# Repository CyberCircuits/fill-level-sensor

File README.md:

Fill-level-sensor
=================

Projects files for roving dynamics ltd, open source fill level sensor (Eagle CAD and MPLAB XC32)

Full details of project can be found at www.rodyne.com

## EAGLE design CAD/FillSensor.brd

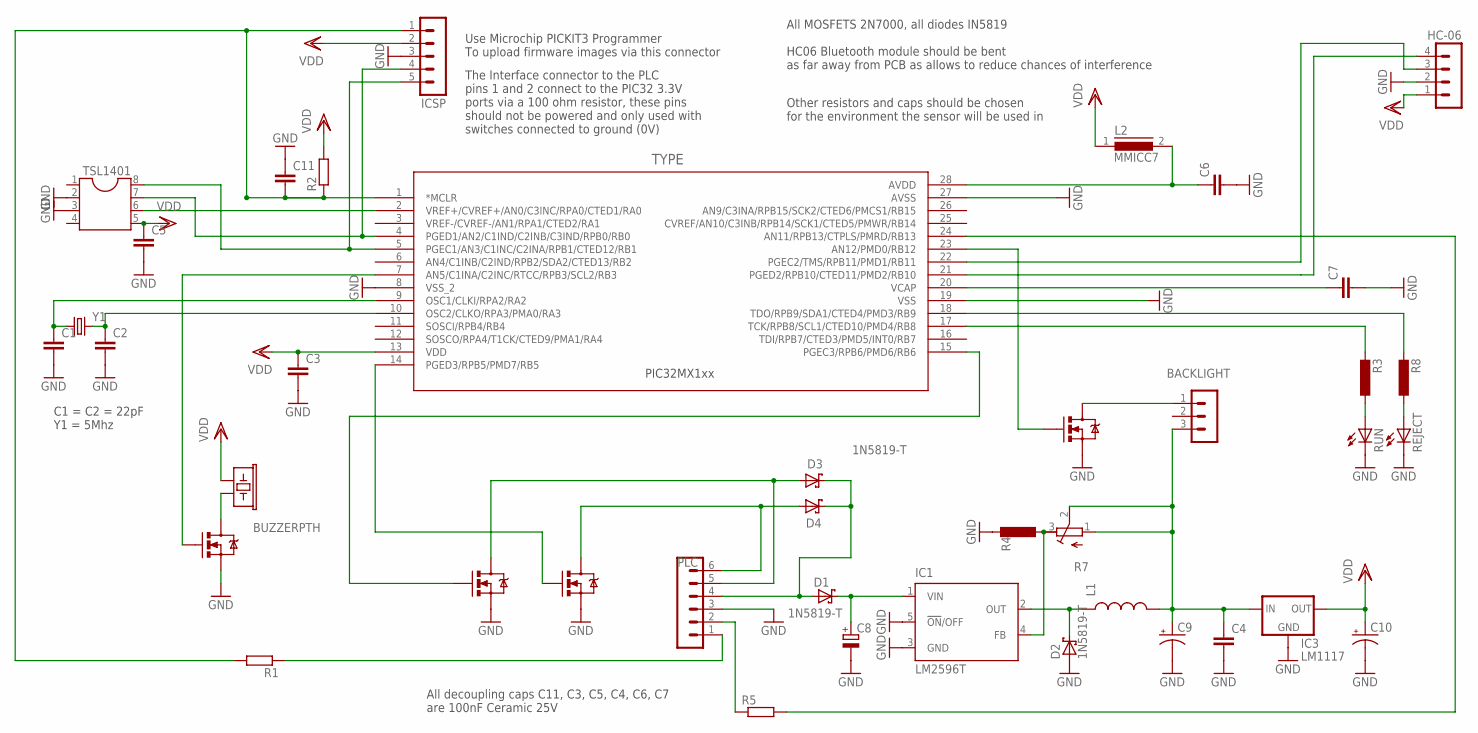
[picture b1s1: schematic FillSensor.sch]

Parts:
BACKLIGHT: MA03-1
C1, C2, C3, C4, C5, C6, C7, C11: CAPPTH; CAP-PTH-SMALL
C8: CPOL-EUE5-5; E5-5
C9, C10: CAP_POLPTH2; CPOL-RADIAL-10UF-25V
D1, D2, D3, D4: 1N5819-T; DO41-7.6
HC-06: MA04-1
IC1: LM2596T; T05D; MPN LM2596T-ADJ/LF02
IC3: LM1117; TO252
ICSP: MA05-1
L1: INDUCTORPWR; CDRH125
L2: MMICC7
PLC: MA06-1
Q1, Q2, Q3, Q4: MOSFET-NCHANNEL2N7000; TO-92-AMMO
R1, R2, R5: R-EU_0207/10; 0207/10
R3, R4, R8: L-EU0207/10; 0207/10
R7: R-TRIMM64W; RTRIM64W
REJECT: LED5MM
RUN: LED5MM
SG1: BUZZERPTH; BUZZER-12MM
TSL1401: DIL8; DIL08
U1: PIC32MX150F128B-; SPDIP28_300MC
Y1: CRYSTALHC49UV; HC49U-V

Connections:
GND: C1.2, C2.2, C3.2, C4.2, C5.2, C6.2, C7.2, C8.-, C9.2 (-), C10.2 (-), C11.1, D2.A, HC-06.2, IC1.3 (GND), IC1.5 (!ON!/OFF), IC3.1 (GND), ICSP.3, PLC.3, Q1.1 (S), Q2.1 (S), Q3.1 (S), Q4.1 (S), R4.1, REJECT.K (C), RUN.K (C), TSL1401.2, TSL1401.3, U1.8 (VSS_2), U1.19 (VSS), U1.27 (AVSS)
unnamed: C1.1, U1.9 (OSC1/CLKI/RPA2/RA2), Y1.1
unnamed: C2.1, U1.10 (OSC2/CLKO/RPA3/PMA0/RA3), Y1.2
unnamed: C6.1, L2.2, U1.28 (AVDD)
unnamed: C11.2, ICSP.1, R1.2, R2.1, U1.1 (*MCLR)
unnamed: TSL1401.6, U1.2 (VREF+/CVREF+/AN0/C3INC/RPA0/CTED1/RA0)
unnamed: R3.1, RUN.A
unnamed: ICSP.5, TSL1401.8, U1.5 (PGEC1/AN3/C1INC/C2INA/RPB1/CTED12/RB1)
unnamed: C7.1, U1.20 (VCAP)
unnamed: Q3.2 (G), U1.23 (AN12/PMD0/RB12)
unnamed: R5.2, U1.24 (AN11/RPB13/CTPLS/PMRD/RB13)
unnamed: ICSP.4, TSL1401.7, U1.4 (PGED1/AN2/C1IND/C2INB/C3IND/RPB0/RB0)
unnamed: R8.1, REJECT.A
unnamed: C8.+, D1.C, IC1.1 (VIN)
unnamed: HC-06.3, U1.22 (PGEC2/TMS/RPB11/PMD1/RB11)
unnamed: IC1.4 (FB), R4.2, R7.3 (A)
unnamed: D4.A, PLC.6, Q1.3 (D)
unnamed: D3.A, PLC.5, Q2.3 (D)
unnamed: Q2.2 (G), U1.15 (PGEC3/RPB6/PMD6/RB6)
unnamed: Q1.2 (G), U1.14 (PGED3/RPB5/PMD7/RB5)
unnamed: BACKLIGHT.3, C4.1, C9.1 (+), IC3.2 (IN), L1.2, R7.1 (E), R7.2 (S)
unnamed: R3.2, U1.17 (TCK/RPB8/SCL1/CTED10/PMD4/RB8)
unnamed: R8.2, U1.18 (TDO/RPB9/SDA1/CTED4/PMD3/RB9)
unnamed: BACKLIGHT.1, Q3.3 (D)
unnamed: HC-06.4, U1.21 (PGED2/RPB10/CTED11/PMD2/RB10)
unnamed: Q4.3 (D), SG1.- (2)
unnamed: Q4.2 (G), U1.7 (AN5/C1INA/C2INC/RTCC/RPB3/SCL2/RB3)
unnamed: D1.A, D3.C, D4.C, PLC.4
unnamed: PLC.1, R1.1
unnamed: PLC.2, R5.1
TH1: D2.C, IC1.2 (OUT), L1.1
VDD: C3.1, C5.1, C10.1 (+), HC-06.1, IC3.TAB (OUT), ICSP.2, L2.1, R2.2, SG1.+ (1), TSL1401.5, U1.13 (VDD)

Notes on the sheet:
PIC32MX1xx
Use Microchip PICKIT3 Programmer To upload firmware images via this connector
All MOSFETS 2N7000, all diodes IN5819 HC06 Bluetooth module should be bent as far away from PCB as allows to reduce chances of interference
C1 = C2 = 22pF Y1 = 5Mhz
All decoupling caps C11, C3, C5, C4, C6, C7 are 100nF Ceramic 25V
The Interface connector to the PLC pins 1 and 2 connect to the PIC32 3.3V ports via a 100 ohm resistor, these pins should not be powered and only used with switches connected to ground (0V)
Other resistors and caps should be chosen for the environment the sensor will be used in

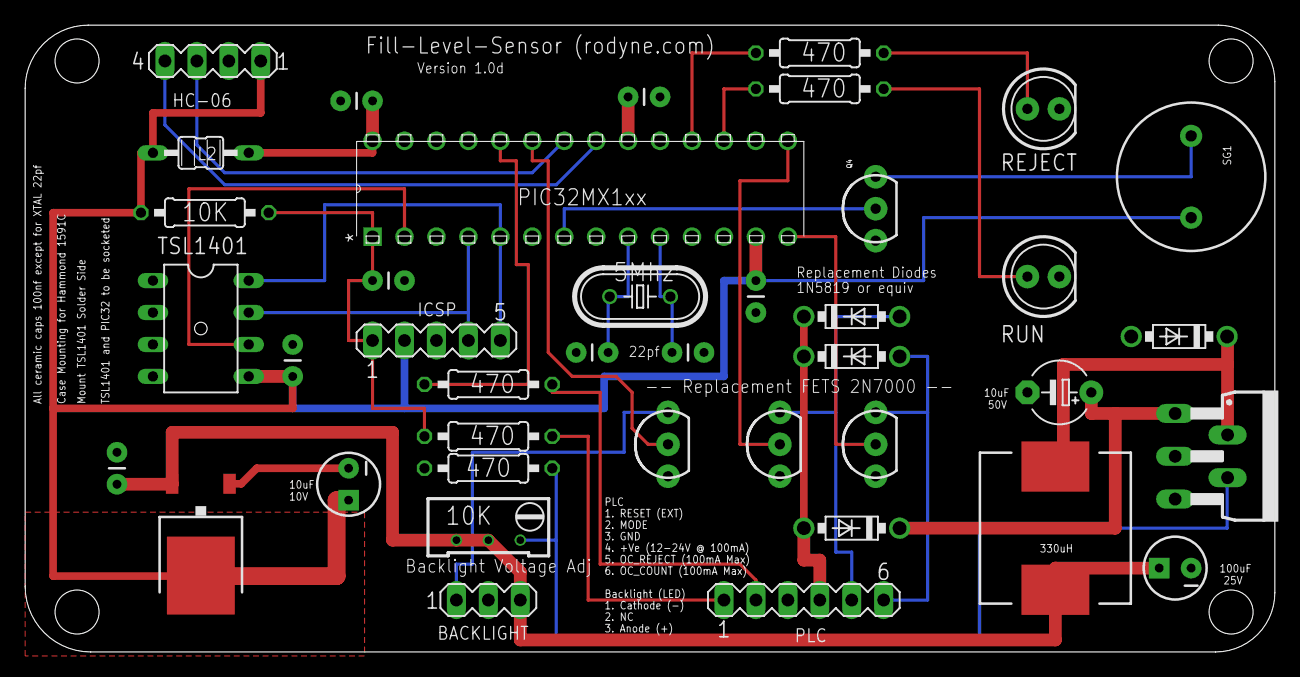
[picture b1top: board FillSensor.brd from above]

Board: 4 copper layers, 99.4 x 49.8 mm, 40 parts (0 on the bottom side), 32 nets.

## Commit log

2014-01-07 Added Working File set from Local PC
    All files required to build project as described on Hack-a-Day on
    2013-01-05

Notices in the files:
parts and their libraries:
SparkFun: Licensing: CC v3.0 Share-Alike You are welcome to use this library for commercial purposes.
